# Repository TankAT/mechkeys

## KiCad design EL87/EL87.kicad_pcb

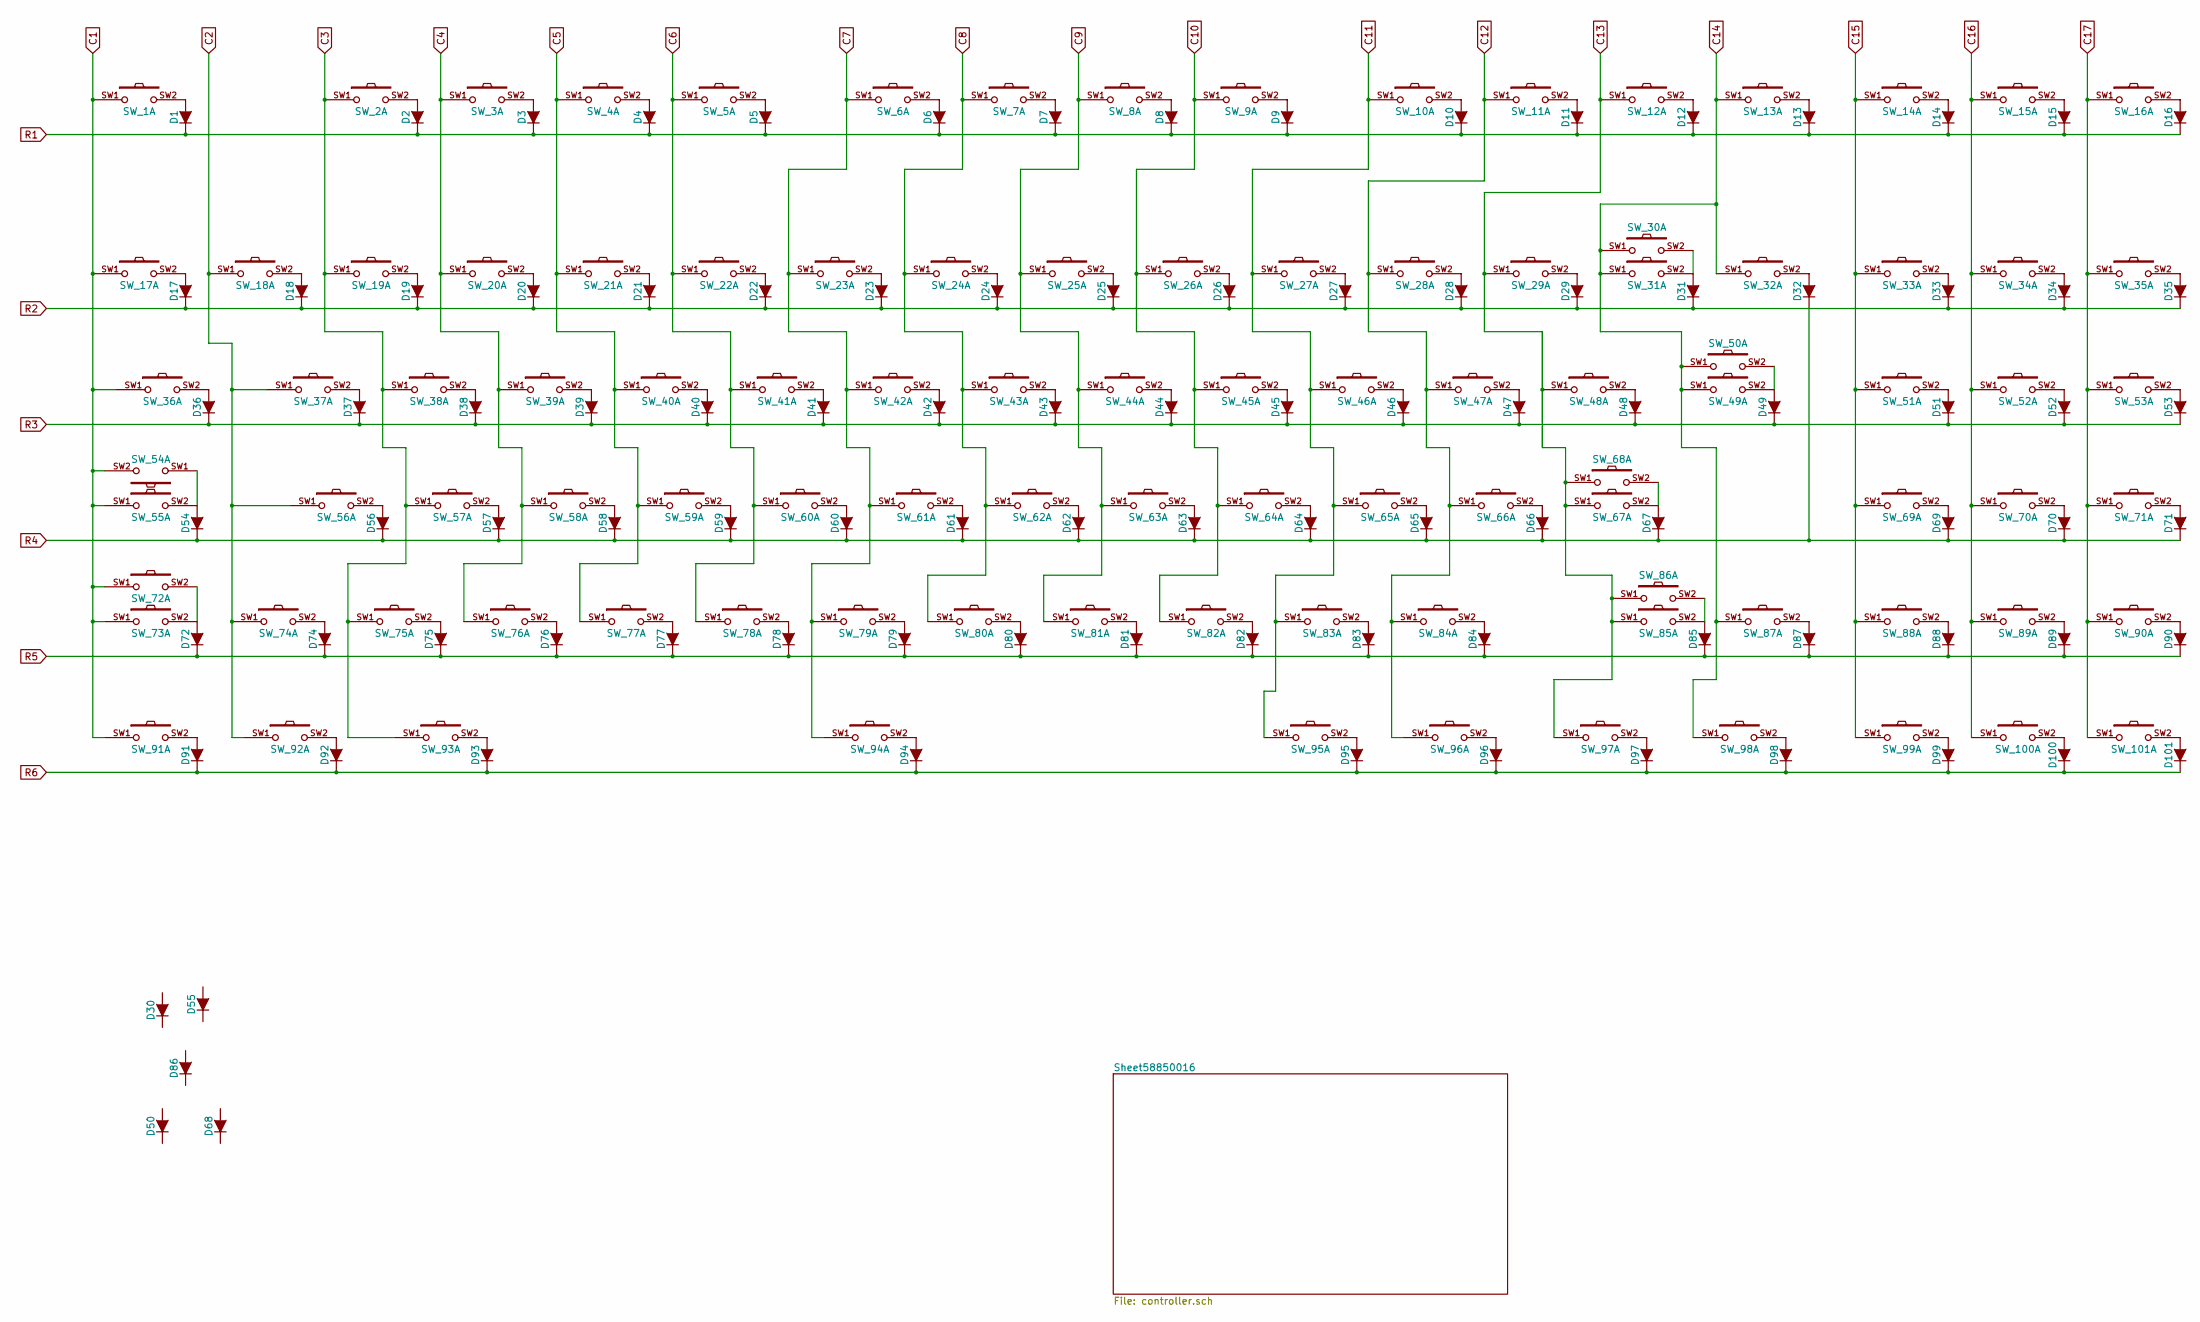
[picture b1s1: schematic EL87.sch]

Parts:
D1, D2, D3, D4, D5, D6, D7, D8, D9, D10, D11, D12, D13, D14, D15, D16, D17, D18, D19, D20, D21, D22, D23, D24, D25, D26, D27, D28, D29, D30, D31, D32, D33, D34, D35, D36, D37, D38, D39, D40, D41, D42, D43, D44, D45, D46, D47, D48, D49, D50, D51, D52, D53, D54, D55, D56, D57, D58, D59, D60, D61, D62, D63, D64, D65, D66, D67, D68, D69, D70, D71, D72, D74, D75, D76, D77, D78, D79, D80, D81, D82, D83, D84, D85, D86, D87, D88, D89, D90, D91, D92, D93, D94, D95, D96, D97, D98, D99, D100, D101: D; MiniMELF_Standard
SW_1, SW_2, SW_3, SW_4, SW_5, SW_6, SW_7, SW_8, SW_9, SW_10, SW_11, SW_12, SW_13, SW_14, SW_15, SW_16, SW_17, SW_18, SW_19, SW_20, SW_21, SW_22, SW_23, SW_24, SW_25, SW_26, SW_27, SW_28, SW_29, SW_30, SW_31, SW_32, SW_33, SW_34, SW_35, SW_36, SW_37, SW_38, SW_39, SW_40, SW_41, SW_42, SW_43, SW_44, SW_45, SW_46, SW_47, SW_48, SW_49, SW_50, SW_51, SW_52, SW_53, SW_54, SW_55, SW_56, SW_57, SW_58, SW_59, SW_60, SW_61, SW_62, SW_63, SW_64, SW_65, SW_66, SW_67, SW_68, SW_69, SW_70, SW_71, SW_72, SW_73, SW_74, SW_75, SW_76, SW_77, SW_78, SW_79, SW_80, SW_81, SW_82, SW_83, SW_84, SW_85, SW_86, SW_87, SW_88, SW_89, SW_90, SW_91, SW_92, SW_93, SW_94, SW_95, SW_96, SW_97, SW_98, SW_99, SW_100, SW_101: MX_LED

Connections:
C1: SW_1.SW1, SW_17.SW1, SW_36.SW1, SW_54.SW2, SW_55.SW1, SW_72.SW1, SW_73.SW1, SW_91.SW1; also elsewhere on the board
C2: SW_18.SW1, SW_37.SW1, SW_56.SW1, SW_74.SW1, SW_92.SW1; also elsewhere on the board
C3: SW_2.SW1, SW_19.SW1, SW_38.SW1, SW_57.SW1, SW_75.SW1, SW_93.SW1; also elsewhere on the board
C4: SW_3.SW1, SW_20.SW1, SW_39.SW1, SW_58.SW1, SW_76.SW1; also elsewhere on the board
C5: SW_4.SW1, SW_21.SW1, SW_40.SW1, SW_59.SW1, SW_77.SW1; also elsewhere on the board
C6: SW_5.SW1, SW_22.SW1, SW_41.SW1, SW_60.SW1, SW_78.SW1; also elsewhere on the board
C7: SW_6.SW1, SW_23.SW1, SW_42.SW1, SW_61.SW1, SW_79.SW1, SW_94.SW1; also elsewhere on the board
C8: SW_7.SW1, SW_24.SW1, SW_43.SW1, SW_62.SW1, SW_80.SW1; also elsewhere on the board
C9: SW_8.SW1, SW_25.SW1, SW_44.SW1, SW_63.SW1, SW_81.SW1; also elsewhere on the board
C10: SW_9.SW1, SW_26.SW1, SW_45.SW1, SW_64.SW1, SW_82.SW1; also elsewhere on the board
C11: SW_10.SW1, SW_27.SW1, SW_46.SW1, SW_65.SW1, SW_83.SW1, SW_95.SW1; also elsewhere on the board
C12: SW_11.SW1, SW_28.SW1, SW_47.SW1, SW_66.SW1, SW_84.SW1, SW_96.SW1; also elsewhere on the board
C13: SW_12.SW1, SW_29.SW1, SW_48.SW1, SW_67.SW1, SW_68.SW1, SW_85.SW1, SW_86.SW1, SW_97.SW1; also elsewhere on the board
C14: SW_13.SW1, SW_30.SW1, SW_31.SW1, SW_32.SW1, SW_49.SW1, SW_50.SW1, SW_87.SW1, SW_98.SW1; also elsewhere on the board
C15: SW_14.SW1, SW_33.SW1, SW_51.SW1, SW_69.SW1, SW_88.SW1, SW_99.SW1; also elsewhere on the board
C16: SW_15.SW1, SW_34.SW1, SW_52.SW1, SW_70.SW1, SW_89.SW1, SW_100.SW1; also elsewhere on the board
C17: SW_16.SW1, SW_35.SW1, SW_53.SW1, SW_71.SW1, SW_90.SW1, SW_101.SW1; also elsewhere on the board
unnamed: D1.2 (A), SW_1.SW2
unnamed: D2.2 (A), SW_2.SW2
unnamed: D3.2 (A), SW_3.SW2
unnamed: D4.2 (A), SW_4.SW2
unnamed: D5.2 (A), SW_5.SW2
unnamed: D6.2 (A), SW_6.SW2
unnamed: D7.2 (A), SW_7.SW2
unnamed: D8.2 (A), SW_8.SW2
unnamed: D9.2 (A), SW_9.SW2
unnamed: D10.2 (A), SW_10.SW2
unnamed: D11.2 (A), SW_11.SW2
unnamed: D12.2 (A), SW_12.SW2
unnamed: D13.2 (A), SW_13.SW2
unnamed: D14.2 (A), SW_14.SW2
unnamed: D15.2 (A), SW_15.SW2
unnamed: D16.2 (A), SW_16.SW2
unnamed: D17.2 (A), SW_17.SW2
unnamed: D18.2 (A), SW_18.SW2
unnamed: D19.2 (A), SW_19.SW2
unnamed: D20.2 (A), SW_20.SW2
unnamed: D21.2 (A), SW_21.SW2
unnamed: D22.2 (A), SW_22.SW2
unnamed: D23.2 (A), SW_23.SW2
unnamed: D24.2 (A), SW_24.SW2
unnamed: D25.2 (A), SW_25.SW2
unnamed: D26.2 (A), SW_26.SW2
unnamed: D27.2 (A), SW_27.SW2
unnamed: D28.2 (A), SW_28.SW2
unnamed: D29.2 (A), SW_29.SW2
unnamed: D31.2 (A), SW_30.SW2, SW_31.SW2
unnamed: D32.2 (A), SW_32.SW2
unnamed: D33.2 (A), SW_33.SW2
unnamed: D34.2 (A), SW_34.SW2
unnamed: D35.2 (A), SW_35.SW2
unnamed: D36.2 (A), SW_36.SW2
unnamed: D37.2 (A), SW_37.SW2
unnamed: D38.2 (A), SW_38.SW2
unnamed: D39.2 (A), SW_39.SW2
unnamed: D40.2 (A), SW_40.SW2
unnamed: D41.2 (A), SW_41.SW2
unnamed: D42.2 (A), SW_42.SW2
unnamed: D43.2 (A), SW_43.SW2
unnamed: D44.2 (A), SW_44.SW2
unnamed: D45.2 (A), SW_45.SW2
unnamed: D46.2 (A), SW_46.SW2
unnamed: D47.2 (A), SW_47.SW2
unnamed: D48.2 (A), SW_48.SW2
unnamed: D49.2 (A), SW_49.SW2, SW_50.SW2
unnamed: D51.2 (A), SW_51.SW2
unnamed: D52.2 (A), SW_52.SW2
unnamed: D53.2 (A), SW_53.SW2
unnamed: D54.2 (A), SW_54.SW1, SW_55.SW2
unnamed: D56.2 (A), SW_56.SW2
unnamed: D57.2 (A), SW_57.SW2
unnamed: D58.2 (A), SW_58.SW2
unnamed: D59.2 (A), SW_59.SW2
unnamed: D60.2 (A), SW_60.SW2
unnamed: D61.2 (A), SW_61.SW2
unnamed: D62.2 (A), SW_62.SW2
unnamed: D63.2 (A), SW_63.SW2
unnamed: D64.2 (A), SW_64.SW2
unnamed: D65.2 (A), SW_65.SW2
unnamed: D66.2 (A), SW_66.SW2
unnamed: D67.2 (A), SW_67.SW2, SW_68.SW2
unnamed: D69.2 (A), SW_69.SW2
unnamed: D70.2 (A), SW_70.SW2
unnamed: D71.2 (A), SW_71.SW2
unnamed: D72.2 (A), SW_72.SW2, SW_73.SW2
unnamed: D74.2 (A), SW_74.SW2
unnamed: D75.2 (A), SW_75.SW2
unnamed: D76.2 (A), SW_76.SW2
unnamed: D77.2 (A), SW_77.SW2
unnamed: D78.2 (A), SW_78.SW2
unnamed: D79.2 (A), SW_79.SW2
unnamed: D80.2 (A), SW_80.SW2
unnamed: D81.2 (A), SW_81.SW2
unnamed: D82.2 (A), SW_82.SW2
unnamed: D83.2 (A), SW_83.SW2
unnamed: D84.2 (A), SW_84.SW2
unnamed: D85.2 (A), SW_85.SW2, SW_86.SW2
unnamed: D87.2 (A), SW_87.SW2
unnamed: D88.2 (A), SW_88.SW2
unnamed: D89.2 (A), SW_89.SW2
unnamed: D90.2 (A), SW_90.SW2
unnamed: D91.2 (A), SW_91.SW2
unnamed: D92.2 (A), SW_92.SW2
unnamed: D93.2 (A), SW_93.SW2
unnamed: D94.2 (A), SW_94.SW2
unnamed: D95.2 (A), SW_95.SW2
unnamed: D96.2 (A), SW_96.SW2
unnamed: D97.2 (A), SW_97.SW2
unnamed: D98.2 (A), SW_98.SW2
unnamed: D99.2 (A), SW_99.SW2
unnamed: D100.2 (A), SW_100.SW2
unnamed: D101.2 (A), SW_101.SW2
R1: D1.1 (K), D2.1 (K), D3.1 (K), D4.1 (K), D5.1 (K), D6.1 (K), D7.1 (K), D8.1 (K), D9.1 (K), D10.1 (K), D11.1 (K), D12.1 (K), D13.1 (K), D14.1 (K), D15.1 (K), D16.1 (K); also elsewhere on the board
R2: D17.1 (K), D18.1 (K), D19.1 (K), D20.1 (K), D21.1 (K), D22.1 (K), D23.1 (K), D24.1 (K), D25.1 (K), D26.1 (K), D27.1 (K), D28.1 (K), D29.1 (K), D31.1 (K), D33.1 (K), D34.1 (K), D35.1 (K); also elsewhere on the board
R3: D36.1 (K), D37.1 (K), D38.1 (K), D39.1 (K), D40.1 (K), D41.1 (K), D42.1 (K), D43.1 (K), D44.1 (K), D45.1 (K), D46.1 (K), D47.1 (K), D48.1 (K), D49.1 (K), D51.1 (K), D52.1 (K), D53.1 (K); also elsewhere on the board
R4: D32.1 (K), D54.1 (K), D56.1 (K), D57.1 (K), D58.1 (K), D59.1 (K), D60.1 (K), D61.1 (K), D62.1 (K), D63.1 (K), D64.1 (K), D65.1 (K), D66.1 (K), D67.1 (K), D69.1 (K), D70.1 (K), D71.1 (K); also elsewhere on the board
R5: D72.1 (K), D74.1 (K), D75.1 (K), D76.1 (K), D77.1 (K), D78.1 (K), D79.1 (K), D80.1 (K), D81.1 (K), D82.1 (K), D83.1 (K), D84.1 (K), D85.1 (K), D87.1 (K), D88.1 (K), D89.1 (K), D90.1 (K); also elsewhere on the board
R6: D91.1 (K), D92.1 (K), D93.1 (K), D94.1 (K), D95.1 (K), D96.1 (K), D97.1 (K), D98.1 (K), D99.1 (K), D100.1 (K), D101.1 (K); also elsewhere on the board

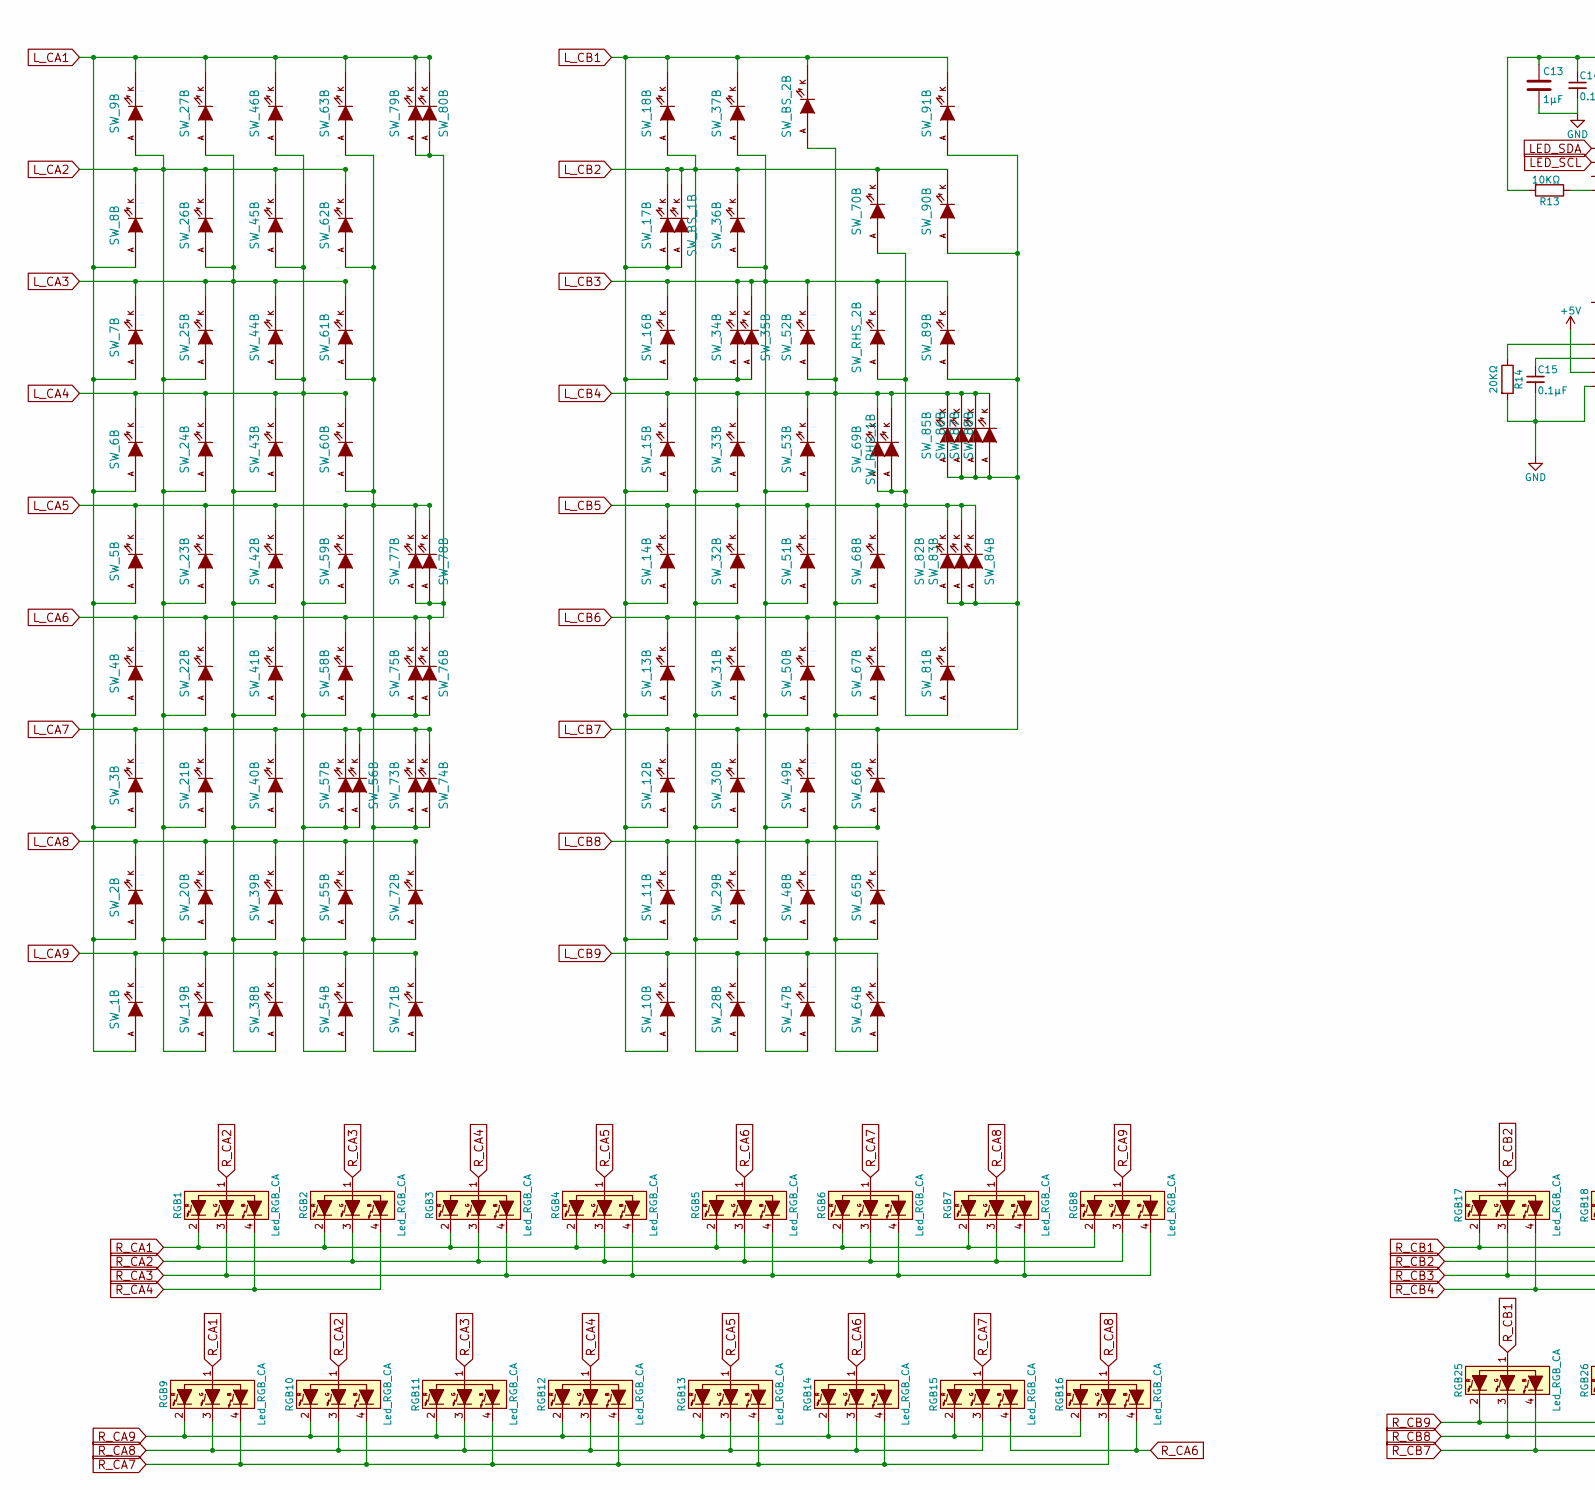
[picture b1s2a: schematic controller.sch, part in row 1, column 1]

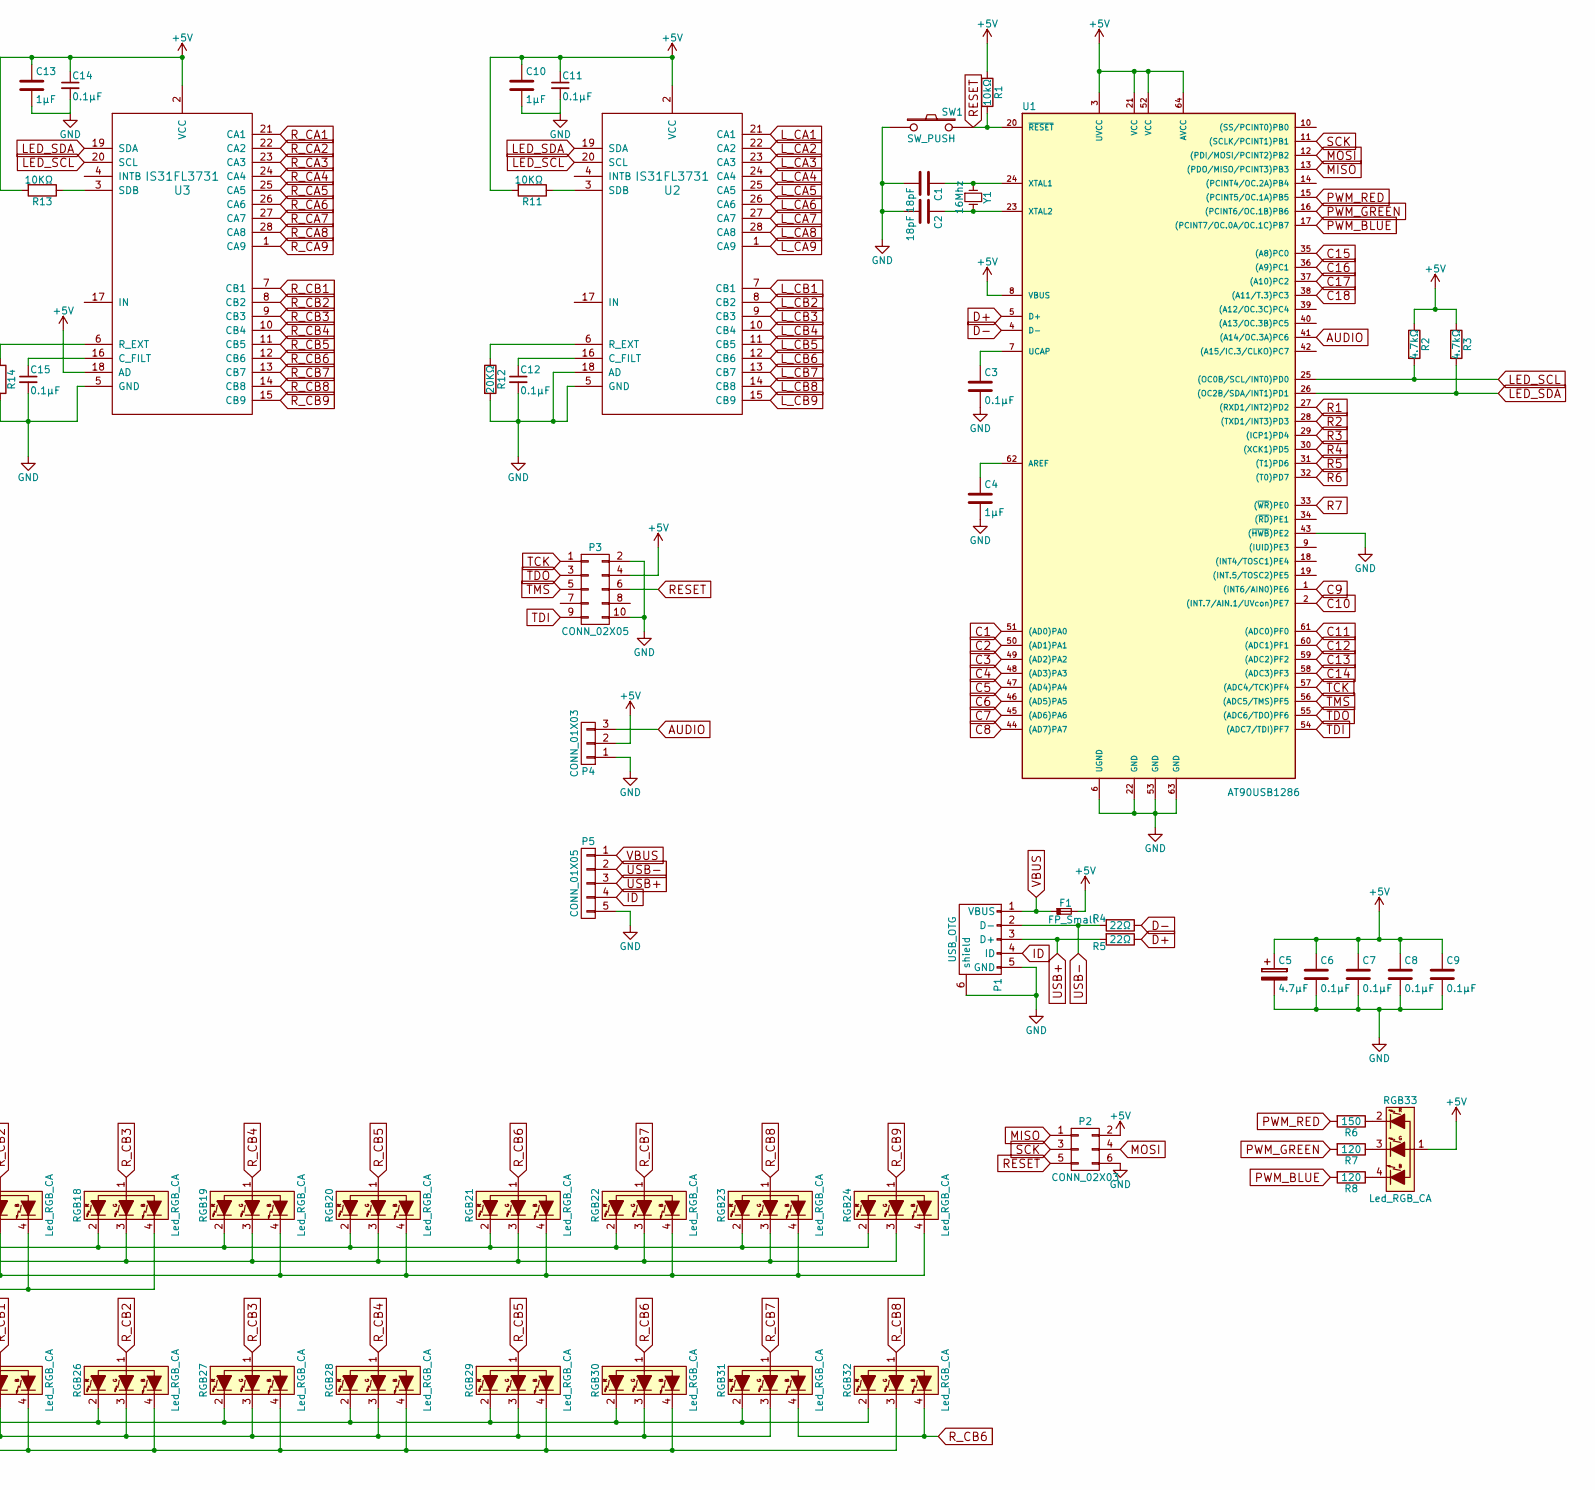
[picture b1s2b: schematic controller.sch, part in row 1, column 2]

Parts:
C1, C2: 18pF; C_0805_HandSoldering
C3, C6, C7, C8, C9, C11, C12, C14, C15: 0.1µF; C_0805_HandSoldering
C4, C10, C13: 1µF; C_0805_HandSoldering
C5: 4.7µF; Tantalum_Case-S_EIA-3216-12_Reflow
F1: FP_Small; R_1206_HandSoldering
P1: USB_OTG; USB_Mini-B
P2: CONN_02X03; Molex_PicoBlade_53261-0671_06x1.25mm_Angled
P3: CONN_02X05; Molex_PicoBlade_53261-1071_10x1.25mm_Angled
P4: CONN_01X03; Molex_PicoBlade_53261-0371_03x1.25mm_Angled
P5: CONN_01X05; Molex_PicoBlade_53261-0571_05x1.25mm_Angled
R1: 10kΩ; R_0805_HandSoldering
R2, R3: 4.7kΩ; R_0805_HandSoldering
R4, R5: 22Ω; R_0805_HandSoldering
R6: 150; R_0805_HandSoldering
R7, R8: 120; R_0805_HandSoldering
R11, R13: 10KΩ; R_0805_HandSoldering
R12, R14: 20KΩ; R_0805_HandSoldering
RGB1, RGB2, RGB3, RGB4, RGB5, RGB6, RGB7, RGB8, RGB9, RGB10, RGB11, RGB12, RGB13, RGB14, RGB15, RGB16, RGB17, RGB18, RGB19, RGB20, RGB21, RGB22, RGB23, RGB24, RGB25, RGB26, RGB27, RGB28, RGB29, RGB30, RGB31, RGB32: Led_RGB_CA; SMP4-RGB
RGB33: Led_RGB_CA; SMP4-RGB-PIPE
SW1: SW_PUSH; SW_SPST_EVQP0
SW_1, SW_2, SW_3, SW_4, SW_5, SW_6, SW_7, SW_8, SW_9, SW_10, SW_11, SW_12, SW_13, SW_14, SW_15, SW_16, SW_17, SW_18, SW_19, SW_20, SW_21, SW_22, SW_23, SW_24, SW_25, SW_26, SW_27, SW_28, SW_29, SW_30, SW_31, SW_32, SW_33, SW_34, SW_35, SW_36, SW_37, SW_38, SW_39, SW_40, SW_41, SW_42, SW_43, SW_44, SW_45, SW_46, SW_47, SW_48, SW_49, SW_50, SW_51, SW_52, SW_53, SW_54, SW_55, SW_56, SW_57, SW_58, SW_59, SW_60, SW_61, SW_62, SW_63, SW_64, SW_65, SW_66, SW_67, SW_68, SW_69, SW_70, SW_71, SW_72, SW_73, SW_74, SW_75, SW_76, SW_77, SW_78, SW_79, SW_80, SW_81, SW_82, SW_83, SW_84, SW_85, SW_86, SW_87, SW_88, SW_89, SW_90, SW_91: MX_LED
SW_BS_1, SW_BS_2: MX_LED
SW_RHS_1, SW_RHS_2: MX_LED
U1: AT90USB1286; TQFP-64_14x14mm_Pitch0.8mm
U2, U3: IS31FL3731; SSOP-28_5.3x10.2mm_Pitch0.65mm
Y1: 16Mhz; Crystal_SMD_5032_4Pads

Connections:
+5V: C5.1, C6.1, C7.1, C8.1, C9.1, C10.1, C11.1, C13.1, C14.1, F1.2, P2.2, P3.4, P4.2, R1.1, R2.1, R3.1, R11.2, R13.2, RGB33.1, U1.3 (UVCC), U1.8 (VBUS), U1.21 (VCC), U1.52 (VCC), U1.64 (AVCC), U2.2 (VCC), U3.2 (VCC), U3.18 (AD)
AUDIO: P4.3, U1.41 ((A14/OC.3A)PC6)
C1: U1.51 ((AD0)PA0); also elsewhere on the board
C2: U1.50 ((AD1)PA1); also elsewhere on the board
C3: U1.49 ((AD2)PA2); also elsewhere on the board
C4: U1.48 ((AD3)PA3); also elsewhere on the board
C5: U1.47 ((AD4)PA4); also elsewhere on the board
C6: U1.46 ((AD5)PA5); also elsewhere on the board
C7: U1.45 ((AD6)PA6); also elsewhere on the board
C8: U1.44 ((AD7)PA7); also elsewhere on the board
C9: U1.1 ((INT6/AIN0)PE6); also elsewhere on the board
C10: U1.2 ((INT.7/AIN.1/UVcon)PE7); also elsewhere on the board
C11: U1.61 ((ADC0)PF0); also elsewhere on the board
C12: U1.60 ((ADC1)PF1); also elsewhere on the board
C13: U1.59 ((ADC2)PF2); also elsewhere on the board
C14: U1.58 ((ADC3)PF3); also elsewhere on the board
C15: U1.35 ((A8)PC0); also elsewhere on the board
C16: U1.36 ((A9)PC1); also elsewhere on the board
C17: U1.37 ((A10)PC2); also elsewhere on the board
C18: U1.38 ((A11/T.3)PC3)
D+: R5.1, U1.5 (D+)
D-: R4.1, U1.4 (D-)
GND: C1.2, C2.2, C3.2, C4.2, C5.2, C6.2, C7.2, C8.2, C9.2, C10.2, C11.2, C12.2, C13.2, C14.2, C15.2, P1.5 (GND), P1.6 (shield), P2.6, P3.2, P3.10, P4.1, P5.5, R12.2, R14.2, SW1.1, U1.6 (UGND), U1.22 (GND), U1.43 ((~HWB~)PE2), U1.53 (GND), U1.63 (GND), U2.5 (GND), U2.18 (AD), U3.5 (GND)
ID: P1.4 (ID), P5.4
LED_SCL: R2.2, U1.25 ((OC0B/SCL/INT0)PD0), U2.20 (SCL), U3.20 (SCL)
LED_SDA: R3.2, U1.26 ((OC2B/SDA/INT1)PD1), U2.19 (SDA), U3.19 (SDA)
L_CA1: SW_1.A, SW_2.A, SW_3.A, SW_4.A, SW_5.A, SW_6.A, SW_7.A, SW_8.A, SW_9.K, SW_27.K, SW_46.K, SW_63.K, SW_79.K, SW_80.K, U2.21 (CA1)
L_CA2: SW_8.K, SW_9.A, SW_19.A, SW_20.A, SW_21.A, SW_22.A, SW_23.A, SW_24.A, SW_25.A, SW_26.K, SW_45.K, SW_62.K, U2.22 (CA2)
L_CA3: SW_7.K, SW_25.K, SW_26.A, SW_27.A, SW_38.A, SW_39.A, SW_40.A, SW_41.A, SW_42.A, SW_43.A, SW_44.K, SW_61.K, U2.23 (CA3)
L_CA4: SW_6.K, SW_24.K, SW_43.K, SW_44.A, SW_45.A, SW_46.A, SW_54.A, SW_55.A, SW_56.A, SW_57.A, SW_58.A, SW_59.A, SW_60.K, U2.24 (CA4)
L_CA5: SW_5.K, SW_23.K, SW_42.K, SW_59.K, SW_60.A, SW_61.A, SW_62.A, SW_63.A, SW_71.A, SW_72.A, SW_73.A, SW_74.A, SW_75.A, SW_76.A, SW_77.K, SW_78.K, U2.25 (CA5)
L_CA6: SW_4.K, SW_22.K, SW_41.K, SW_58.K, SW_75.K, SW_76.K, SW_77.A, SW_78.A, SW_79.A, SW_80.A, U2.26 (CA6)
L_CA7: SW_3.K, SW_21.K, SW_40.K, SW_56.K, SW_57.K, SW_73.K, SW_74.K, U2.27 (CA7)
L_CA8: SW_2.K, SW_20.K, SW_39.K, SW_55.K, SW_72.K, U2.28 (CA8)
L_CA9: SW_1.K, SW_19.K, SW_38.K, SW_54.K, SW_71.K, U2.1 (CA9)
L_CB1: SW_10.A, SW_11.A, SW_12.A, SW_13.A, SW_14.A, SW_15.A, SW_16.A, SW_17.A, SW_18.K, SW_37.K, SW_91.K, SW_BS_1.A, SW_BS_2.K, U2.7 (CB1)
L_CB2: SW_17.K, SW_18.A, SW_28.A, SW_29.A, SW_30.A, SW_31.A, SW_32.A, SW_33.A, SW_34.A, SW_35.A, SW_36.K, SW_70.K, SW_90.K, SW_BS_1.K, U2.8 (CB2)
L_CB3: SW_16.K, SW_34.K, SW_35.K, SW_36.A, SW_37.A, SW_47.A, SW_48.A, SW_49.A, SW_50.A, SW_51.A, SW_52.K, SW_53.A, SW_89.K, SW_RHS_2.K, U2.9 (CB3)
L_CB4: SW_15.K, SW_33.K, SW_52.A, SW_53.K, SW_64.A, SW_65.A, SW_66.A, SW_67.A, SW_68.A, SW_69.K, SW_85.K, SW_86.K, SW_87.K, SW_88.K, SW_BS_2.A, SW_RHS_1.K, U2.10 (CB4)
L_CB5: SW_14.K, SW_32.K, SW_51.K, SW_68.K, SW_69.A, SW_70.A, SW_81.A, SW_82.K, SW_83.K, SW_84.K, SW_RHS_1.A, SW_RHS_2.A, U2.11 (CB5)
L_CB6: SW_13.K, SW_31.K, SW_50.K, SW_67.K, SW_81.K, U2.12 (CB6)
L_CB7: SW_12.K, SW_30.K, SW_49.K, SW_66.K, SW_82.A, SW_83.A, SW_84.A, SW_85.A, SW_86.A, SW_87.A, SW_88.A, SW_89.A, SW_90.A, SW_91.A, U2.13 (CB7)
L_CB8: SW_11.K, SW_29.K, SW_48.K, SW_65.K, U2.14 (CB8)
L_CB9: SW_10.K, SW_28.K, SW_47.K, SW_64.K, U2.15 (CB9)
MISO: P2.1, U1.13 ((PDO/MISO/PCINT3)PB3)
MOSI: P2.4, U1.12 ((PDI/MOSI/PCINT2)PB2)
unnamed: C1.1, U1.24 (XTAL1), Y1.1
unnamed: C2.1, U1.23 (XTAL2), Y1.2
unnamed: C3.1, U1.7 (UCAP)
unnamed: C4.1, U1.62 (AREF)
unnamed: C12.1, U2.16 (C_FILT)
unnamed: C15.1, U3.16 (C_FILT)
unnamed: R6.1, RGB33.2 (R)
unnamed: R7.1, RGB33.3 (G)
unnamed: R8.1, RGB33.4 (B)
unnamed: R11.1, U2.3 (SDB)
unnamed: R12.1, U2.6 (R_EXT)
unnamed: R13.1, U3.3 (SDB)
unnamed: R14.1, U3.6 (R_EXT)
PWM_BLUE: R8.2, U1.17 ((PCINT7/OC.0A/OC.1C)PB7)
PWM_GREEN: R7.2, U1.16 ((PCINT6/OC.1B)PB6)
PWM_RED: R6.2, U1.15 ((PCINT5/OC.1A)PB5)
R1: U1.27 ((RXD1/INT2)PD2); also elsewhere on the board
R2: U1.28 ((TXD1/INT3)PD3); also elsewhere on the board
R3: U1.29 ((ICP1)PD4); also elsewhere on the board
R4: U1.30 ((XCK1)PD5); also elsewhere on the board
R5: U1.31 ((T1)PD6); also elsewhere on the board
R6: U1.32 ((T0)PD7); also elsewhere on the board
R7: U1.33 ((~WR~)PE0)
RESET: P2.5, P3.6, R1.2, SW1.2, U1.20 (~RESET~)
R_CA1: RGB1.2 (R), RGB2.2 (R), RGB3.2 (R), RGB4.2 (R), RGB5.2 (R), RGB6.2 (R), RGB7.2 (R), RGB8.2 (R), RGB9.1, U3.21 (CA1)
R_CA2: RGB1.1, RGB2.3 (G), RGB3.3 (G), RGB4.3 (G), RGB5.3 (G), RGB6.3 (G), RGB7.3 (G), RGB8.3 (G), RGB10.1, U3.22 (CA2)
R_CA3: RGB1.3 (G), RGB2.1, RGB3.4 (B), RGB4.4 (B), RGB5.4 (B), RGB6.4 (B), RGB7.4 (B), RGB8.4 (B), RGB11.1, U3.23 (CA3)
R_CA4: RGB1.4 (B), RGB2.4 (B), RGB3.1, RGB12.1, U3.24 (CA4)
R_CA5: RGB4.1, RGB13.1, U3.25 (CA5)
R_CA6: RGB5.1, RGB14.1, RGB15.4 (B), RGB16.4 (B), U3.26 (CA6)
R_CA7: RGB6.1, RGB9.4 (B), RGB10.4 (B), RGB11.4 (B), RGB12.4 (B), RGB13.4 (B), RGB14.4 (B), RGB15.1, RGB16.3 (G), U3.27 (CA7)
R_CA8: RGB7.1, RGB9.3 (G), RGB10.3 (G), RGB11.3 (G), RGB12.3 (G), RGB13.3 (G), RGB14.3 (G), RGB15.3 (G), RGB16.1, U3.28 (CA8)
R_CA9: RGB8.1, RGB9.2 (R), RGB10.2 (R), RGB11.2 (R), RGB12.2 (R), RGB13.2 (R), RGB14.2 (R), RGB15.2 (R), RGB16.2 (R), U3.1 (CA9)
R_CB1: RGB17.2 (R), RGB18.2 (R), RGB19.2 (R), RGB20.2 (R), RGB21.2 (R), RGB22.2 (R), RGB23.2 (R), RGB24.2 (R), RGB25.1, U3.7 (CB1)
R_CB2: RGB17.1, RGB18.3 (G), RGB19.3 (G), RGB20.3 (G), RGB21.3 (G), RGB22.3 (G), RGB23.3 (G), RGB24.3 (G), RGB26.1, U3.8 (CB2)
R_CB3: RGB17.3 (G), RGB18.1, RGB19.4 (B), RGB20.4 (B), RGB21.4 (B), RGB22.4 (B), RGB23.4 (B), RGB24.4 (B), RGB27.1, U3.9 (CB3)
R_CB4: RGB17.4 (B), RGB18.4 (B), RGB19.1, RGB28.1, U3.10 (CB4)
R_CB5: RGB20.1, RGB29.1, U3.11 (CB5)
R_CB6: RGB21.1, RGB30.1, RGB31.4 (B), RGB32.4 (B), U3.12 (CB6)
R_CB7: RGB22.1, RGB25.4 (B), RGB26.4 (B), RGB27.4 (B), RGB28.4 (B), RGB29.4 (B), RGB30.4 (B), RGB31.1, RGB32.3 (G), U3.13 (CB7)
R_CB8: RGB23.1, RGB25.3 (G), RGB26.3 (G), RGB27.3 (G), RGB28.3 (G), RGB29.3 (G), RGB30.3 (G), RGB31.3 (G), RGB32.1, U3.14 (CB8)
R_CB9: RGB24.1, RGB25.2 (R), RGB26.2 (R), RGB27.2 (R), RGB28.2 (R), RGB29.2 (R), RGB30.2 (R), RGB31.2 (R), RGB32.2 (R), U3.15 (CB9)
SCK: P2.3, U1.11 ((SCLK/PCINT1)PB1)
TCK: P3.1, U1.57 ((ADC4/TCK)PF4)
TDI: P3.9, U1.54 ((ADC7/TDI)PF7)
TDO: P3.3, U1.55 ((ADC6/TDO)PF6)
TMS: P3.5, U1.56 ((ADC5/TMS)PF5)
USB+: P1.3 (D+), P5.3, R5.2
USB-: P1.2 (D-), P5.2, R4.2
VBUS: F1.1, P1.1 (VBUS), P5.1

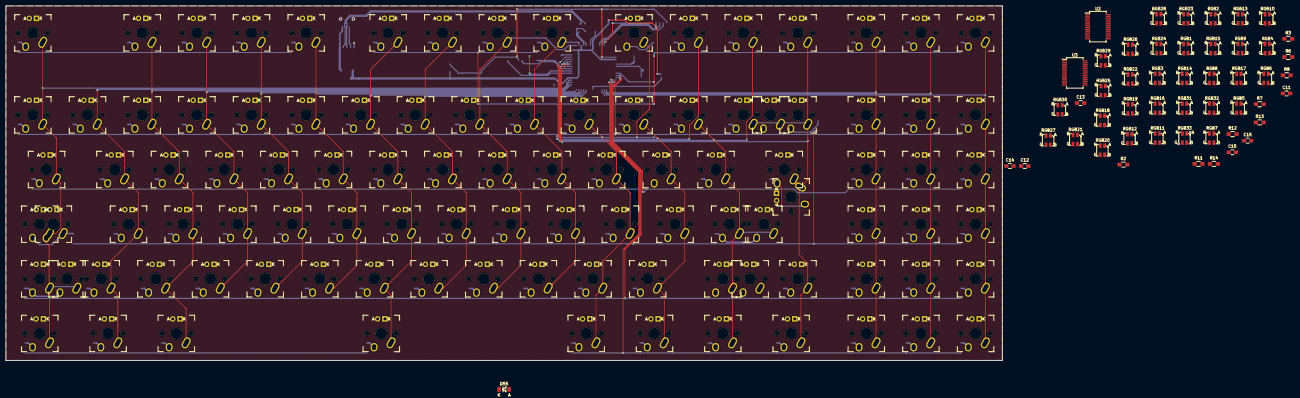
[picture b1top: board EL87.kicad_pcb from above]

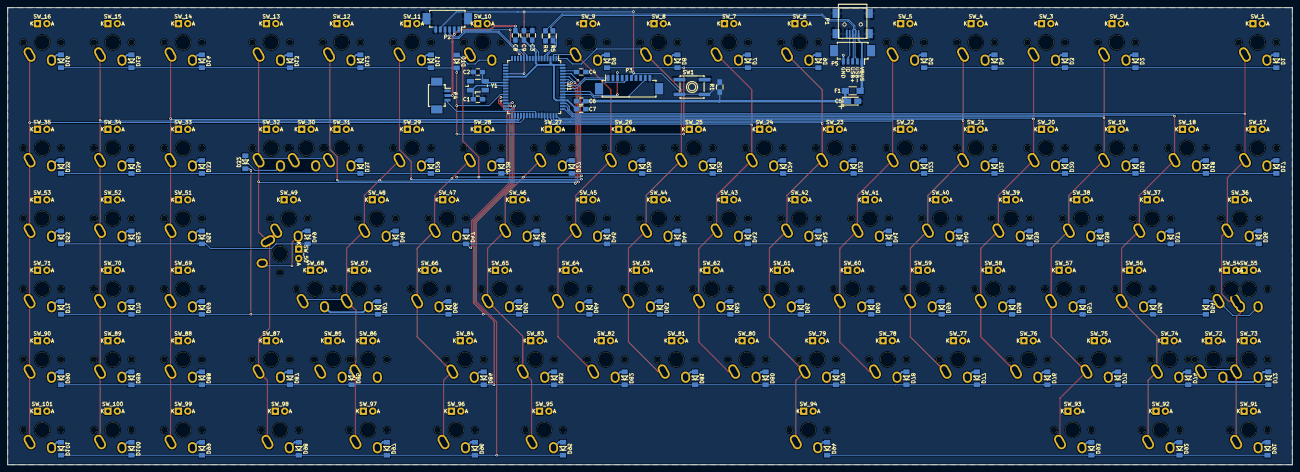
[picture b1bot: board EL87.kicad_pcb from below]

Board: 2 copper layers, 347.3 x 123.6 mm, 268 parts (116 on the bottom side), 189 nets.

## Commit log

2017-01-28 Preliminary PCB layout
2017-01-28 Switch matrix complete.
